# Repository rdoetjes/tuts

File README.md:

# Tutorial collection

In the underlying directories, you will find software I have written for training videos and other tutorials.
Many of these videos are on https://www.youtube.com/channel/CallousCoder 

Many different languages are covered, ranging from MUMPS (M) to modern day languages like Zig (which I adore) and Rust.
All these tutorials are based around small (private) projects, that I either created purposely for videos or have been created for small private projects.

## DOS Assembly coding vidos

## SPEED HACKS

## ARM64 Assembly coding videos

## ARM32 Assembly coding videos

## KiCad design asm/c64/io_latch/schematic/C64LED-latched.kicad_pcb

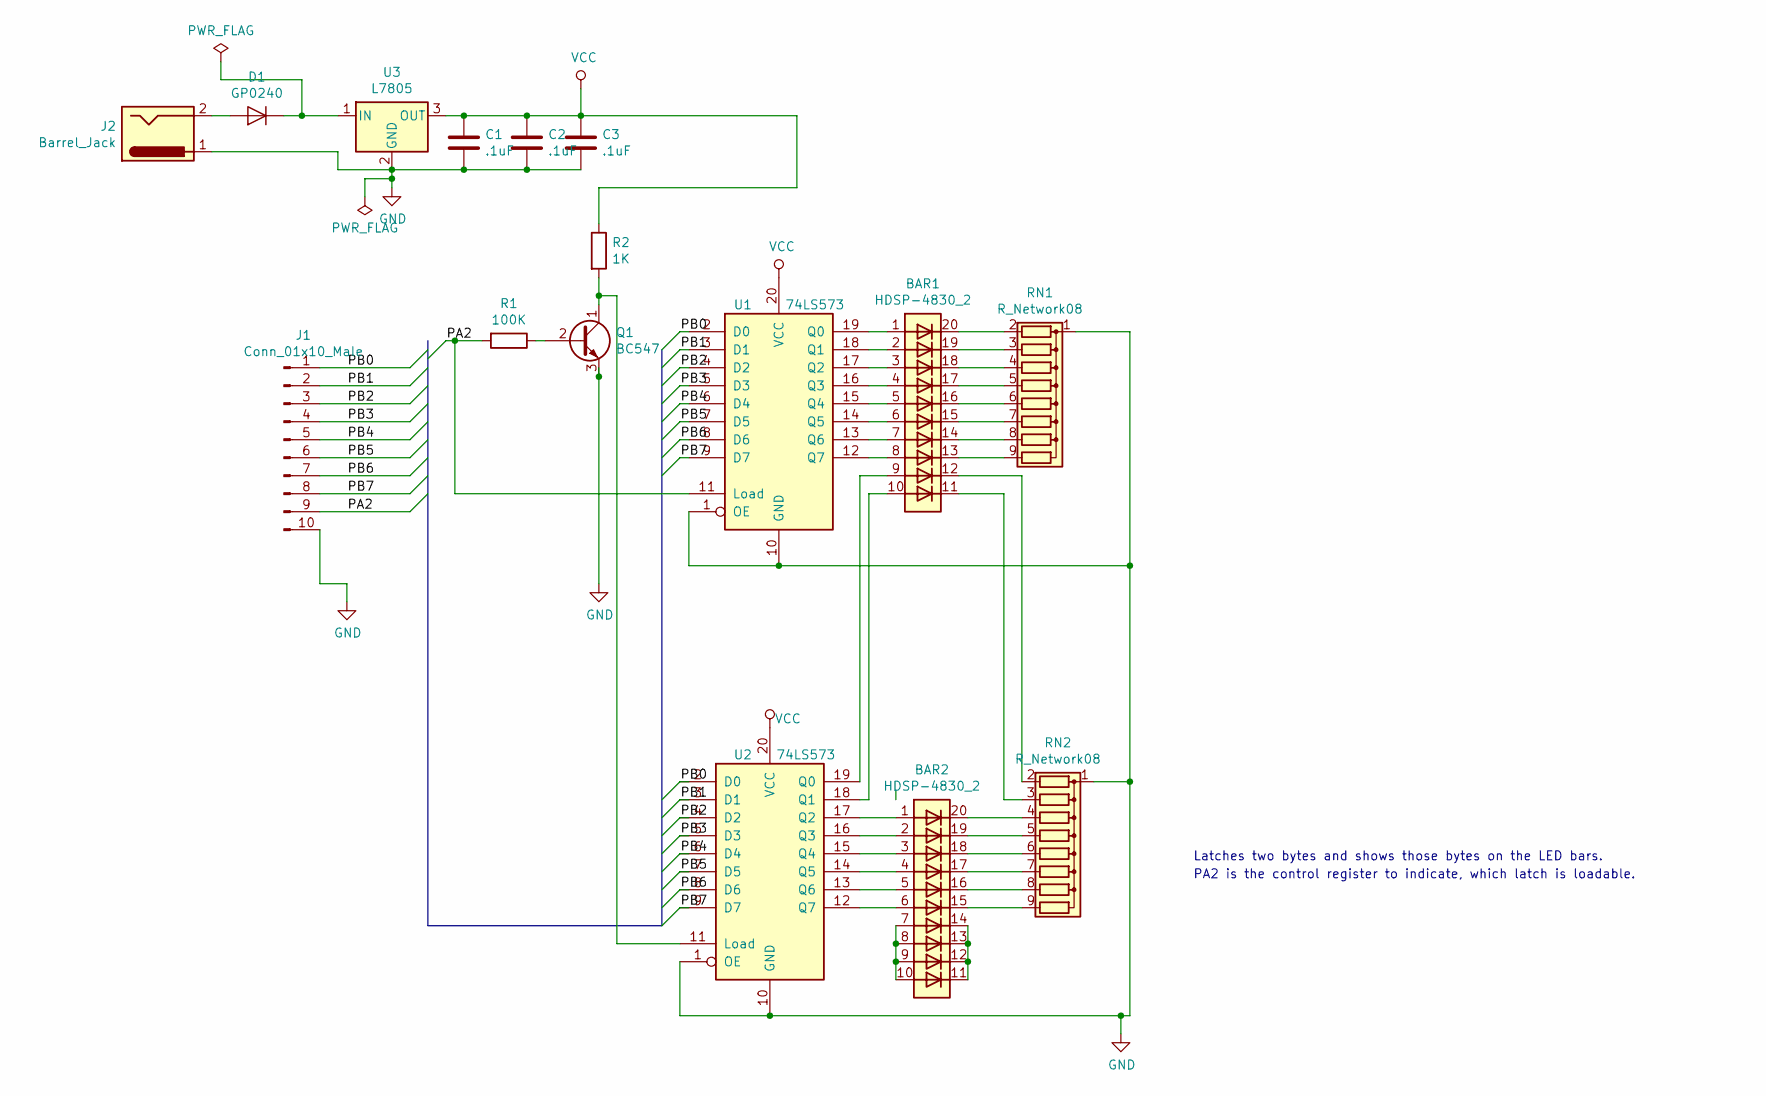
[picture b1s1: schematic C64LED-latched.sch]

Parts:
BAR1, BAR2: HDSP-4830_2; HDSP-4830
C1: .1uF; C_Disc_D6.0mm_W2.5mm_P5.00mm
C2, C3: .1uF; C_Disc_D5.0mm_W2.5mm_P2.50mm
D1: GP0240; D_DO-34_SOD68_P7.62mm_Horizontal
J1: Conn_01x10_Male; PinHeader_1x10_P2.54mm_Vertical
J2: Barrel_Jack; BarrelJack_CUI_PJ-063AH_Horizontal_CircularHoles
Q1: BC547; TO-92_Inline
R1: 100K; R_Axial_DIN0204_L3.6mm_D1.6mm_P5.08mm_Horizontal
R2: 1K; R_Axial_DIN0204_L3.6mm_D1.6mm_P5.08mm_Horizontal
RN1, RN2: R_Network08; R_Array_SIP9
U1, U2: 74LS573; DIP-20_W7.62mm_Socket
U3: L7805; TO-220-3_Vertical

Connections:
/PA2: J1.9, R1.2, U1.11 (Load)
/PB0: J1.1, U1.2 (D0), U2.2 (D0)
/PB1: J1.2, U1.3 (D1), U2.3 (D1)
/PB2: J1.3, U1.4 (D2), U2.4 (D2)
/PB3: J1.4, U1.5 (D3), U2.5 (D3)
/PB4: J1.5, U1.6 (D4), U2.6 (D4)
/PB5: J1.6, U1.7 (D5), U2.7 (D5)
/PB6: J1.7, U1.8 (D6), U2.8 (D6)
/PB7: J1.8, U1.9 (D7), U2.9 (D7)
GND: C1.2, C2.2, C3.2, J1.10, J2.1, Q1.3 (E), RN1.1 (common), RN2.1 (common), U1.1 (OE), U1.10 (GND), U2.1 (OE), U2.10 (GND), U3.2 (GND)
unnamed: BAR1.1 (A), U1.19 (Q0)
unnamed: BAR1.2 (A), U1.18 (Q1)
unnamed: BAR1.3 (A), U1.17 (Q2)
unnamed: BAR1.4 (A), U1.16 (Q3)
unnamed: BAR1.5 (A), U1.15 (Q4)
unnamed: BAR1.6 (A), U1.14 (Q5)
unnamed: BAR1.7 (A), U1.13 (Q6)
unnamed: BAR1.8 (A), U1.12 (Q7)
unnamed: BAR1.9 (A), U2.19 (Q0)
unnamed: BAR1.10 (A), U2.18 (Q1)
unnamed: BAR1.11 (K), RN2.3 (R2)
unnamed: BAR1.12 (K), RN2.2 (R1)
unnamed: BAR1.13 (K), RN1.9 (R8)
unnamed: BAR1.14 (K), RN1.8 (R7)
unnamed: BAR1.15 (K), RN1.7 (R6)
unnamed: BAR1.16 (K), RN1.6 (R5)
unnamed: BAR1.17 (K), RN1.5 (R4)
unnamed: BAR1.18 (K), RN1.4 (R3)
unnamed: BAR1.19 (K), RN1.3 (R2)
unnamed: BAR1.20 (K), RN1.2 (R1)
unnamed: BAR2.1 (A), U2.17 (Q2)
unnamed: BAR2.2 (A), U2.16 (Q3)
unnamed: BAR2.3 (A), U2.15 (Q4)
unnamed: BAR2.4 (A), U2.14 (Q5)
unnamed: BAR2.5 (A), U2.13 (Q6)
unnamed: BAR2.6 (A), U2.12 (Q7)
unnamed: BAR2.7 (A), BAR2.8 (A), BAR2.9 (A), BAR2.10 (A)
unnamed: BAR2.11 (K), BAR2.12 (K), BAR2.13 (K), BAR2.14 (K)
unnamed: BAR2.15 (K), RN2.9 (R8)
unnamed: BAR2.16 (K), RN2.8 (R7)
unnamed: BAR2.17 (K), RN2.7 (R6)
unnamed: BAR2.18 (K), RN2.6 (R5)
unnamed: BAR2.19 (K), RN2.5 (R4)
unnamed: BAR2.20 (K), RN2.4 (R3)
unnamed: D1.1 (K), U3.1 (IN)
unnamed: D1.2 (A), J2.2
unnamed: Q1.1 (C), R2.2, U2.11 (Load)
unnamed: Q1.2 (B), R1.1
VCC: C1.1, C2.1, C3.1, R2.1, U1.20 (VCC), U2.20 (VCC), U3.3 (OUT)

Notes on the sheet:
Latches two bytes and shows those bytes on the LED bars.
PA2 is the control register to indicate, which latch is loadable.

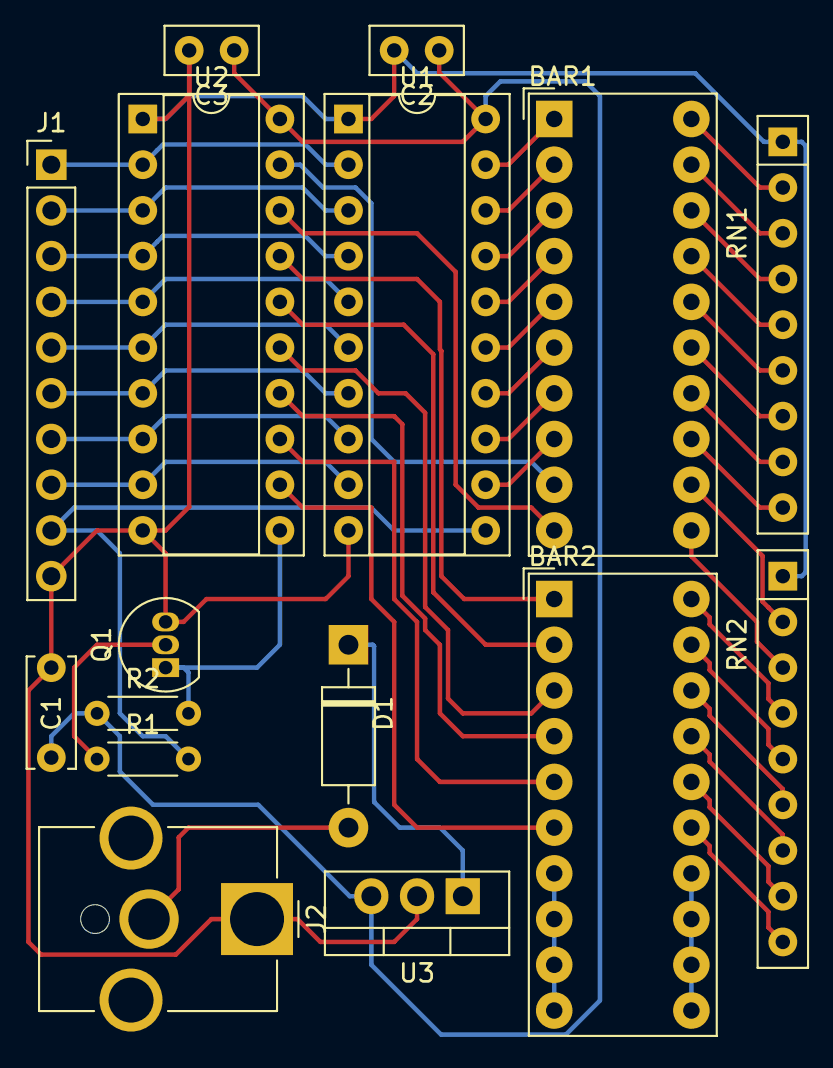
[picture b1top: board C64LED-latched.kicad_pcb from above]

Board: 2 copper layers, 16 parts (0 on the bottom side), 49 nets.

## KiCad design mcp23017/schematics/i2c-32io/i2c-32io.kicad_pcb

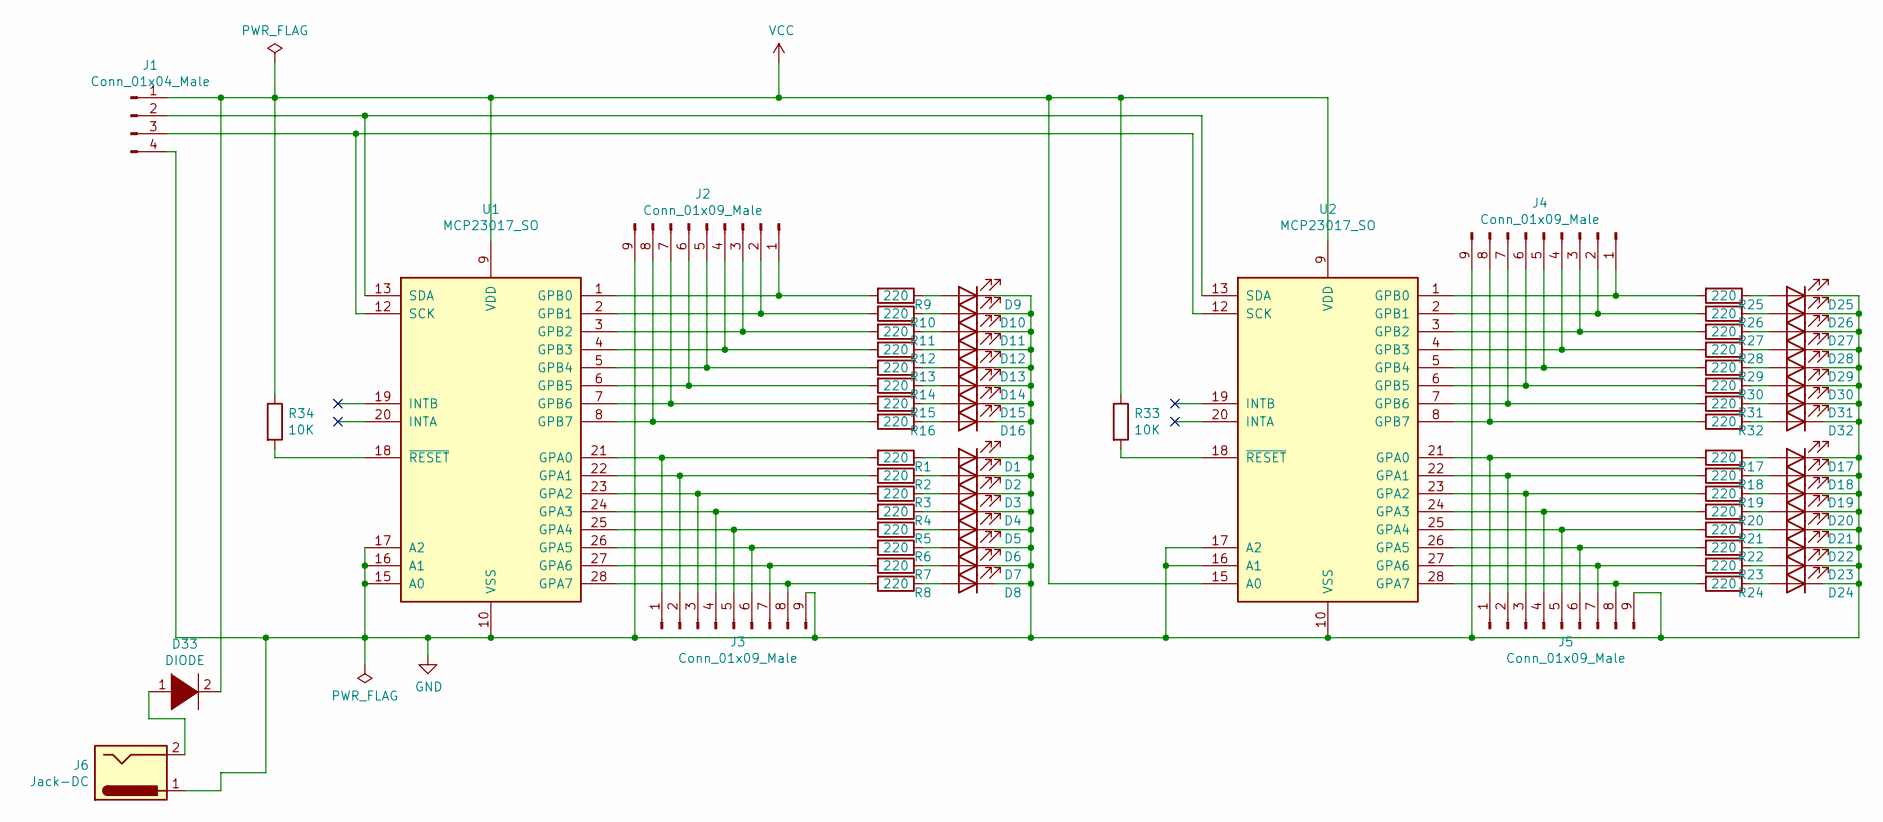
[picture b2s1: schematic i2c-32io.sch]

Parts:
D1, D2, D3, D4, D5, D6, D7, D8, D9, D10, D11, D12, D13, D14, D15, D16, D17, D18, D19, D20, D21, D22, D23, D24, D25, D26, D27, D28, D29, D30, D31, D32: LED; LED_1206_3216Metric
D33: DIODE; D_DO-35_SOD27_P12.70mm_Horizontal
J1: Conn_01x04_Male; PinHeader_1x04_P2.54mm_Vertical
J2, J3, J4, J5: Conn_01x09_Male; PinHeader_1x09_P2.54mm_Vertical
J6: Jack-DC; BarrelJack_CUI_PJ-063AH_Horizontal_CircularHoles
R1, R2, R3, R4, R5, R6, R7, R8, R9, R10, R11, R12, R13, R14, R15, R16, R17, R18, R19, R20, R21, R22, R23, R24, R25, R26, R27, R28, R29, R30, R31, R32: 220; R_1206_3216Metric
R33, R34: 10K; R_1206_3216Metric
U1, U2: MCP23017_SO; SOIC-28W_7.5x17.9mm_P1.27mm

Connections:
unnamed: D1.2 (A), R1.1
unnamed: D2.2 (A), R2.1
unnamed: D3.2 (A), R3.1
unnamed: D4.2 (A), R4.1
unnamed: D5.2 (A), R5.1
unnamed: D6.2 (A), R6.1
unnamed: D7.2 (A), R7.1
unnamed: D8.2 (A), R8.1
unnamed: D9.2 (A), R9.1
unnamed: D10.2 (A), R10.1
unnamed: D11.2 (A), R11.1
unnamed: D12.2 (A), R12.1
unnamed: D13.2 (A), R13.1
unnamed: D14.2 (A), R14.1
unnamed: D15.2 (A), R15.1
unnamed: D16.2 (A), R16.1
unnamed: D17.2 (A), R17.1
unnamed: D18.2 (A), R18.1
unnamed: D19.2 (A), R19.1
unnamed: D20.2 (A), R20.1
unnamed: D21.2 (A), R21.1
unnamed: D22.2 (A), R22.1
unnamed: D23.2 (A), R23.1
unnamed: D24.2 (A), R24.1
unnamed: D25.2 (A), R25.1
unnamed: D26.2 (A), R26.1
unnamed: D27.2 (A), R27.1
unnamed: D28.2 (A), R28.1
unnamed: D29.2 (A), R29.1
unnamed: D30.2 (A), R30.1
unnamed: D31.2 (A), R31.1
unnamed: D32.2 (A), R32.1
unnamed: D33.1 (K), J6.2
unnamed: J1.2, U1.13 (SDA), U2.13 (SDA)
unnamed: J1.3, U1.12 (SCK), U2.12 (SCK)
unnamed: J2.1, R9.2, U1.1 (GPB0)
unnamed: J2.2, R10.2, U1.2 (GPB1)
unnamed: J2.3, R11.2, U1.3 (GPB2)
unnamed: J2.4, R12.2, U1.4 (GPB3)
unnamed: J2.5, R13.2, U1.5 (GPB4)
unnamed: J2.6, R14.2, U1.6 (GPB5)
unnamed: J2.7, R15.2, U1.7 (GPB6)
unnamed: J2.8, R16.2, U1.8 (GPB7)
unnamed: J3.1, R1.2, U1.21 (GPA0)
unnamed: J3.2, R2.2, U1.22 (GPA1)
unnamed: J3.3, R3.2, U1.23 (GPA2)
unnamed: J3.4, R4.2, U1.24 (GPA3)
unnamed: J3.5, R5.2, U1.25 (GPA4)
unnamed: J3.6, R6.2, U1.26 (GPA5)
unnamed: J3.7, R7.2, U1.27 (GPA6)
unnamed: J3.8, R8.2, U1.28 (GPA7)
unnamed: J4.1, R25.2, U2.1 (GPB0)
unnamed: J4.2, R26.2, U2.2 (GPB1)
unnamed: J4.3, R27.2, U2.3 (GPB2)
unnamed: J4.4, R28.2, U2.4 (GPB3)
unnamed: J4.5, R29.2, U2.5 (GPB4)
unnamed: J4.6, R30.2, U2.6 (GPB5)
unnamed: J4.7, R31.2, U2.7 (GPB6)
unnamed: J4.8, R32.2, U2.8 (GPB7)
unnamed: J5.1, R17.2, U2.21 (GPA0)
unnamed: J5.2, R18.2, U2.22 (GPA1)
unnamed: J5.3, R19.2, U2.23 (GPA2)
unnamed: J5.4, R20.2, U2.24 (GPA3)
unnamed: J5.5, R21.2, U2.25 (GPA4)
unnamed: J5.6, R22.2, U2.26 (GPA5)
unnamed: J5.7, R23.2, U2.27 (GPA6)
unnamed: J5.8, R24.2, U2.28 (GPA7)
unnamed: R33.2, U2.18 (~RESET~)
unnamed: R34.2, U1.18 (~RESET~)

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
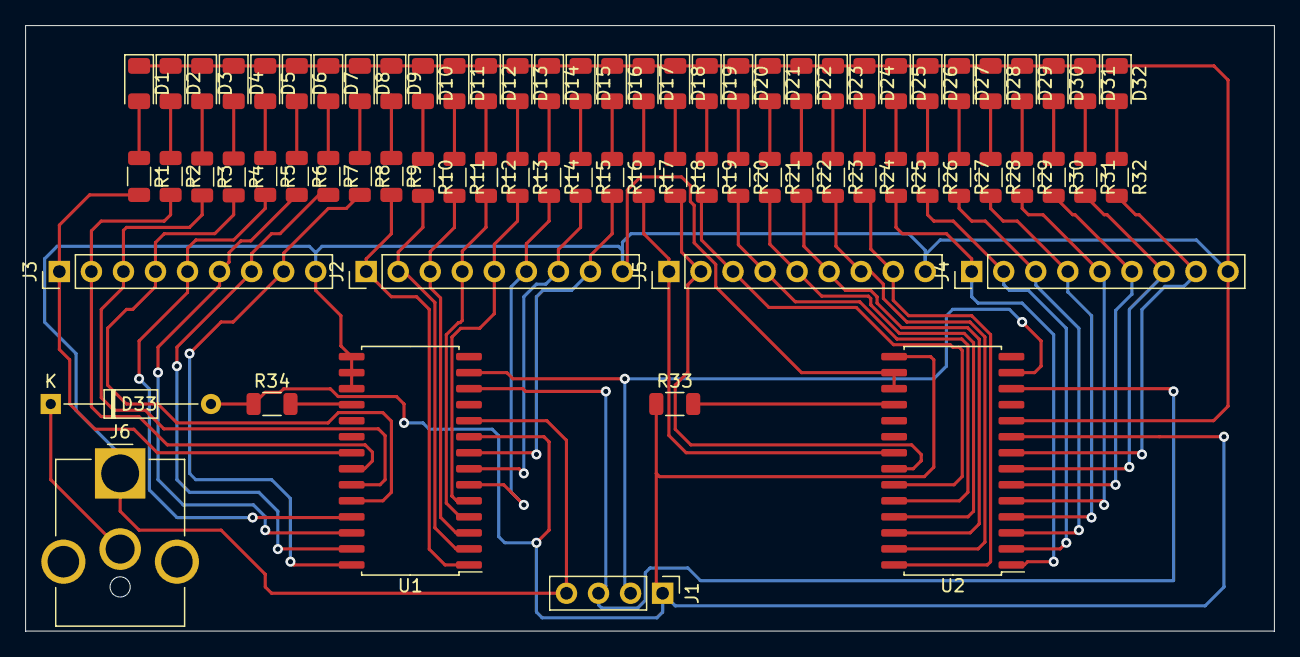
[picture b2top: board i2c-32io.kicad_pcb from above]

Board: 2 copper layers, 99.0 x 48.0 mm, 75 parts (0 on the bottom side), 71 nets.

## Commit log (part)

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2025-12-12 moved calculate to own function
2025-12-12 readme added pointer
2025-12-12 renamed fucntiom
2025-12-12 extensive documentation
2025-12-12 docu
2025-12-12 moved helps into a directory
2025-12-12 moved into dir
2025-12-12 remover
2025-12-12 docs: add comments and examples to ConvertCIDRToIPNetmask
2025-12-12 added make file
2025-12-15 docs: add documentation for CalculateBroadcastAddress and update CalculateNetworkAddress
2025-12-15 single purpose
2025-12-15 added make test
2025-12-15 added integration test
2025-12-16 renamed test file
2025-12-16 just some text
2025-12-16 input valIDATIN USING REGEGX
2025-12-16 docs
2025-12-16 made input validation better so that it checks the string format and then the octets, that way 000 is okay which with just a regex is not okay
2025-12-16 error string
2025-12-16 changed functioname
2025-12-16 better name for function
2025-12-16 title extended
2025-12-16 error message
2025-12-16 integration tests extended with errornous input
2025-12-16 renmed integration tests
2025-12-16 force retest when running make test
2025-12-16 changed test output ALL TO T.*
2025-12-16 run all tests in all dirs
2025-12-16 make install script and documetatopm
2025-12-16 documentaion
2025-12-16 Windows build also made, apparently IT studens use Windows laptops... *SIGH WE ARE LOST* :)
2025-12-16 readme
2025-12-16 missed a printf
2025-12-16 extended the documentatiom
2025-12-16 split out octet and cidr mask functions, in case we need to reuse then at a point
2025-12-16 added explicit error retruns in the golang mindset
2025-12-16 error strings and tests updated to match
2025-12-16 explicit error messages
2025-12-16 remark
2025-12-16 remarrk
2025-12-16 tests
2025-12-16 more explicit error message
2025-12-16 ignore err in test (if it breaks then fine) makes the code less dense
2025-12-16 godoc format
2025-12-19 order of operations
2025-12-19 removed unneceassry assignment
2025-12-20 added api end point
2025-12-20 added api endpoint
2025-12-20 added idr test for rest
2025-12-20 funcitons above main
2025-12-25 knights tour
2025-12-25 arguments
2026-01-14 dded check
2026-01-22 Fixed Makefile and wall satify clangd
2026-02-27 added answering machine brute force
2026-02-27 created a rough connect 4
2026-02-27 code
2026-02-27 added config struct
2026-02-27 moveed logic into seperate files
2026-02-27 Make clean
2026-03-01 send and flush
2026-03-01 ICRNL enabled for loop back to work....
2026-03-01 debug logging
2026-03-01 screen loogging
2026-03-06 bluebox
2026-03-07 AT wasn't required
2026-03-07 Tone dialing works
2026-03-07 Added > to wait for keyboard
2026-03-07 add demo dials
2026-03-07 demo with comments
2026-03-07 Update national_call_kp1
2026-03-07 Update international_transit_kp2
2026-03-07 Create mary_had_alittle_lamb
2026-03-07 55ms instead of 50 ms
2026-03-07 settle alsa initi to prevent partially swalling first tone..
2026-03-07 update settle timeout
2026-03-07 removed reduendancy
2026-03-07 wait init to 500ms
2026-03-08 added sezie added wait milliseocnds added demo
2026-03-08 typo fixed
2026-03-08 Demo comments
2026-03-08 added comment
2026-03-08 removed PK1 PL2
2026-03-08 removed unused header
2026-03-08 alignmenyt of if blocks
2026-03-08 comments
2026-03-08 comment
2026-03-09 mukti hop example
2026-03-09 added rust n eddy wares
2026-03-10 rusty and edy
2026-03-10 added readme
2026-03-10 added video
2026-04-11 added bruteforce pin 2 and 3 long
2026-04-11 print dialed tones
2026-04-11 added shell script to generate bruteforce dial
2026-04-11 explanation of bruteforce_generate_pins_and_dial.sh
2026-04-11 add dial number first
2026-04-12 removed bruteforce_2_digit_pin not needed
2026-04-12 added # in password demo and put dial in var (more efficient)
2026-04-12 remarks
2026-04-12 moved dial strings into a variable, easy to change when needed
2026-04-12 remark typo
2026-04-13 added hangup
2026-04-13 implemneted hangup over serial
2026-04-13 readme and H command print
2026-04-13 added H TIMEOUT_MS PAUSE_MS
2026-04-13 moved parse and play function in thieir own funcitons
2026-04-13 H command and moved if blocks into their own function
2026-04-13 made dedicated 2 pin with and without hangup disabled hangup in the bruteforce generator
2026-04-15 test plit up AI
2026-04-15 split up files
2026-04-15 fixed print
2026-04-15 defualt device goed gezet
2026-04-15 readme fixed
2026-04-15 Moved the dial files into a directory
2026-04-15 moved dial files into their own directory
2026-04-15 readme reverted
2026-04-15 made dtmf the same as c5 in function layout
2026-04-15 split inot smakler files
2026-04-15 split a function up
2026-04-15 moved definition from header to cpp since its a local function
2026-04-15 removed description
2026-04-16 added envelope attack and decay
2026-04-16 Sample rate
2026-04-20 just a code obfusecation for a demo
2026-04-20 demo
2026-04-20 audio cracker
2026-04-20 audio hack
2026-04-26 match camera PRNU
2026-04-26 template_enginer added
2026-04-26 readme example
2026-04-26 added flag for parameter parsing (makes order no longer required)
2026-04-26 added strict mode
2026-04-26 push added missing replace for example
2026-04-26 a and p are the same
2026-04-26 Created an Args struct that we fill in, so we can move the ParseArguments in it's own function and pass the args struct pointer to have it fill it in
2026-04-26 just dropped the var for :=
2026-04-26 added an include
2026-04-26 added an incliude
2026-04-26 enforce include to only have .json extension
2026-04-26 readme added include_ example
2026-04-27 replace more than ones
2026-04-27 default name conevntion
2026-05-17 Very simple rudimentary forth in rp2040
2026-05-17 add scripts
2026-05-17 if then
2026-05-17 bug fix if then
2026-05-17 auto tests
2026-05-17 auto test
2026-05-17 ." " added
2026-05-17 removed print
2026-05-17 variable added
2026-05-17 2drop
2026-05-17 preprocessor so we can use eal forth in the assmebly
2026-05-17 / div added
2026-05-17 tests with asserts
2026-05-18 removed ; multi statements
2026-05-18 reset gpio
2026-05-18 added set_pin_to
2026-05-18 timer added
2026-05-18 timmer added
2026-05-18 New Forth Words
    1. **`MS_SLEEP`**
    * **Stack Effect**: `( ms -- )`
    * **Description**: Pauses execution for the specified number of
    milliseconds using the RP2040 hardware timer for high accuracy.
    * **Safety**: Automatically detects if running in QEMU (where the
    hardware timer isn't available) and skips the wait to prevent
2026-05-18 added uf2 conversion
2026-05-18 make uf2 immediately
2026-05-18 make pico added
2026-05-18 removed macros we do not use
2026-05-18 set led on when initialised
2026-05-18 boot fuxed
2026-05-18 calc checksum
2026-05-18 checksujm
2026-05-18 do not override UART pin settings and start at GPIO28 that's the only
2026-05-18 higher order fuctions inown file forth_words.sinc which is preporcessed
2026-05-18 added higher order function into their own file
2026-05-18 added higher order function in it's own file
2026-05-18 greater than
2026-05-18 Using char literals for r0 emit
2026-05-18 boot2.bin with 256 bytes still hangs at boot
2026-05-18 added the pico-sdk boot code
2026-05-18 uf2 added since it's a target platform so why not deliver the binary?
2026-05-18 added the uf2
2026-05-19 moved boot.inc into boot.s compile and link with boot.o as startup
2026-05-19 Make and link file changed so that make pico used pico_booth is at 0x10000000 and is 256 (f0) bytes long
